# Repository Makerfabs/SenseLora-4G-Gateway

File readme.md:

# SenseLoRa 4G Gateway

```c++
/*
Version:		V1.0
Author:			Vincent
Create Date:	2024/6/19
Note:

*/
```
# Makerfabs

[Makerfabs home page](https://www.makerfabs.com/)

[Makerfabs Wiki](https://wiki.makerfabs.com/)

# How To Use

## Arduino Complier Option

**If you have any questions，such as how to install the development board, how to download the code, how to install the library. Please refer to :[Makerfabs_FAQ](https://github.com/Makerfabs/Makerfabs_FAQ)**

- Install board : ESP32 Version 2.0.11
- Select "ESP32-S3"
- Select Erase All Flash
- Upload codes

Arduino libraries:

- RadioLib 4.6.0

## Example

### fw_test

The factory test program detects whether the AT module can search for the operator and receives Lora data in a loop.

### at_test

Used to debug the AT module and perform transparent serial port transmission.

### lora2thingspeak

The JSON data from the SenseLora Air Monitor is parsed and forwarded to ThingSpeak.

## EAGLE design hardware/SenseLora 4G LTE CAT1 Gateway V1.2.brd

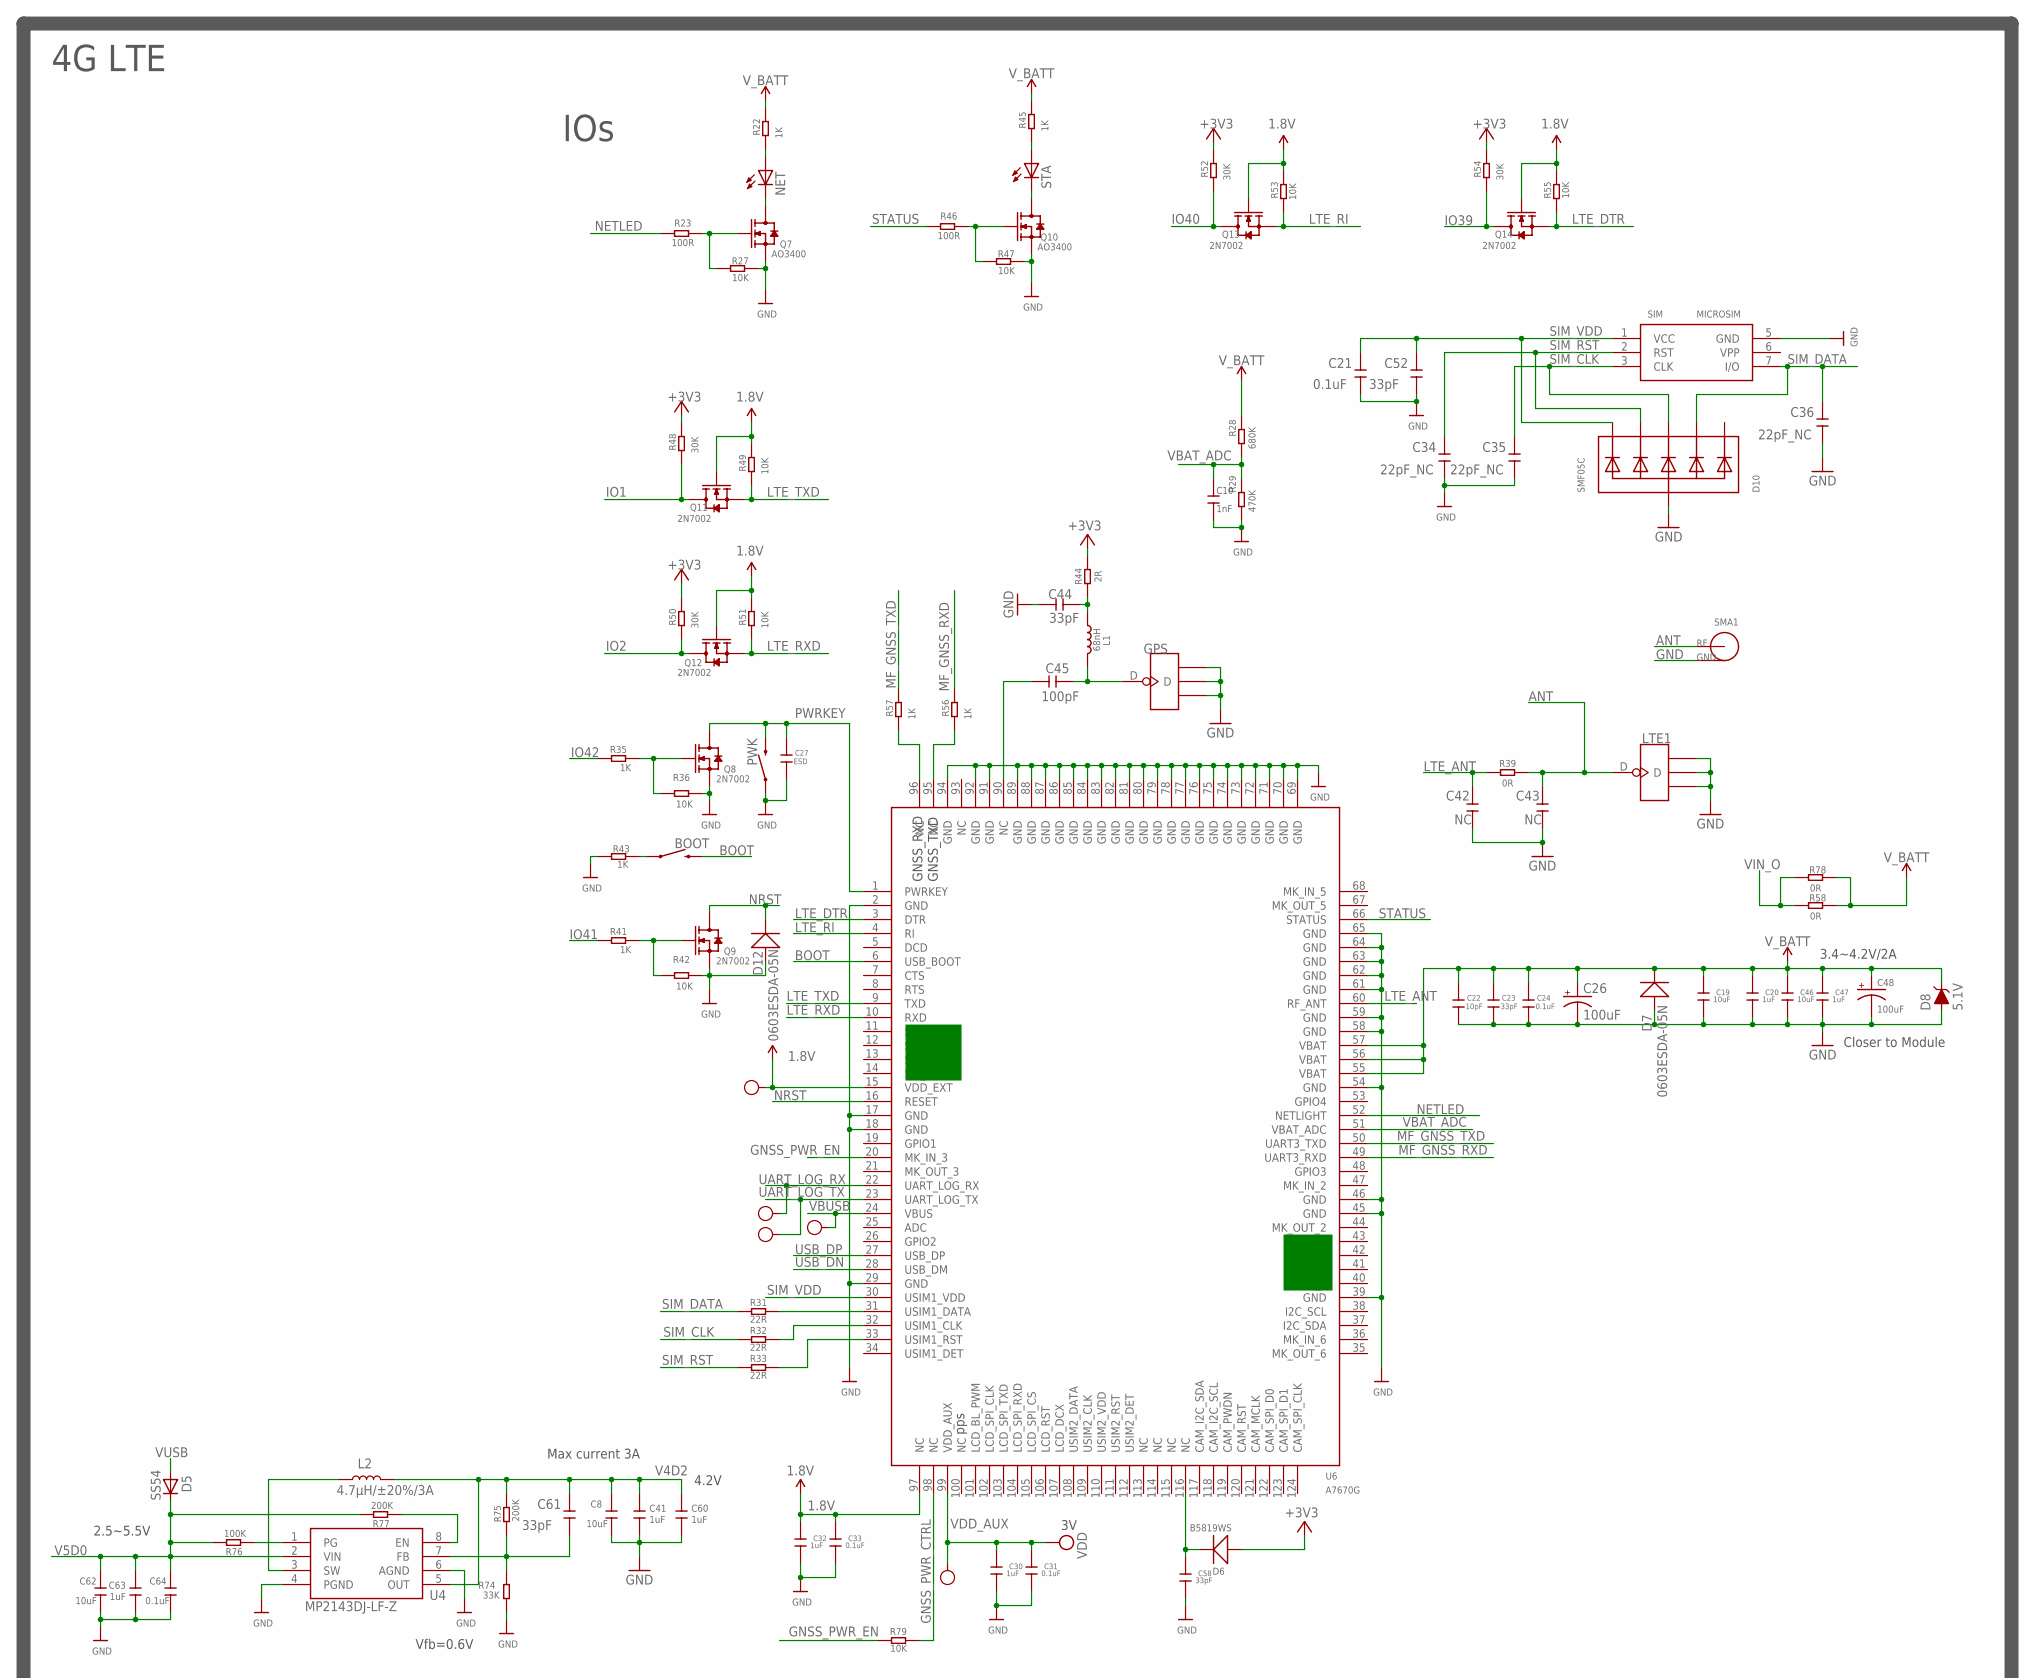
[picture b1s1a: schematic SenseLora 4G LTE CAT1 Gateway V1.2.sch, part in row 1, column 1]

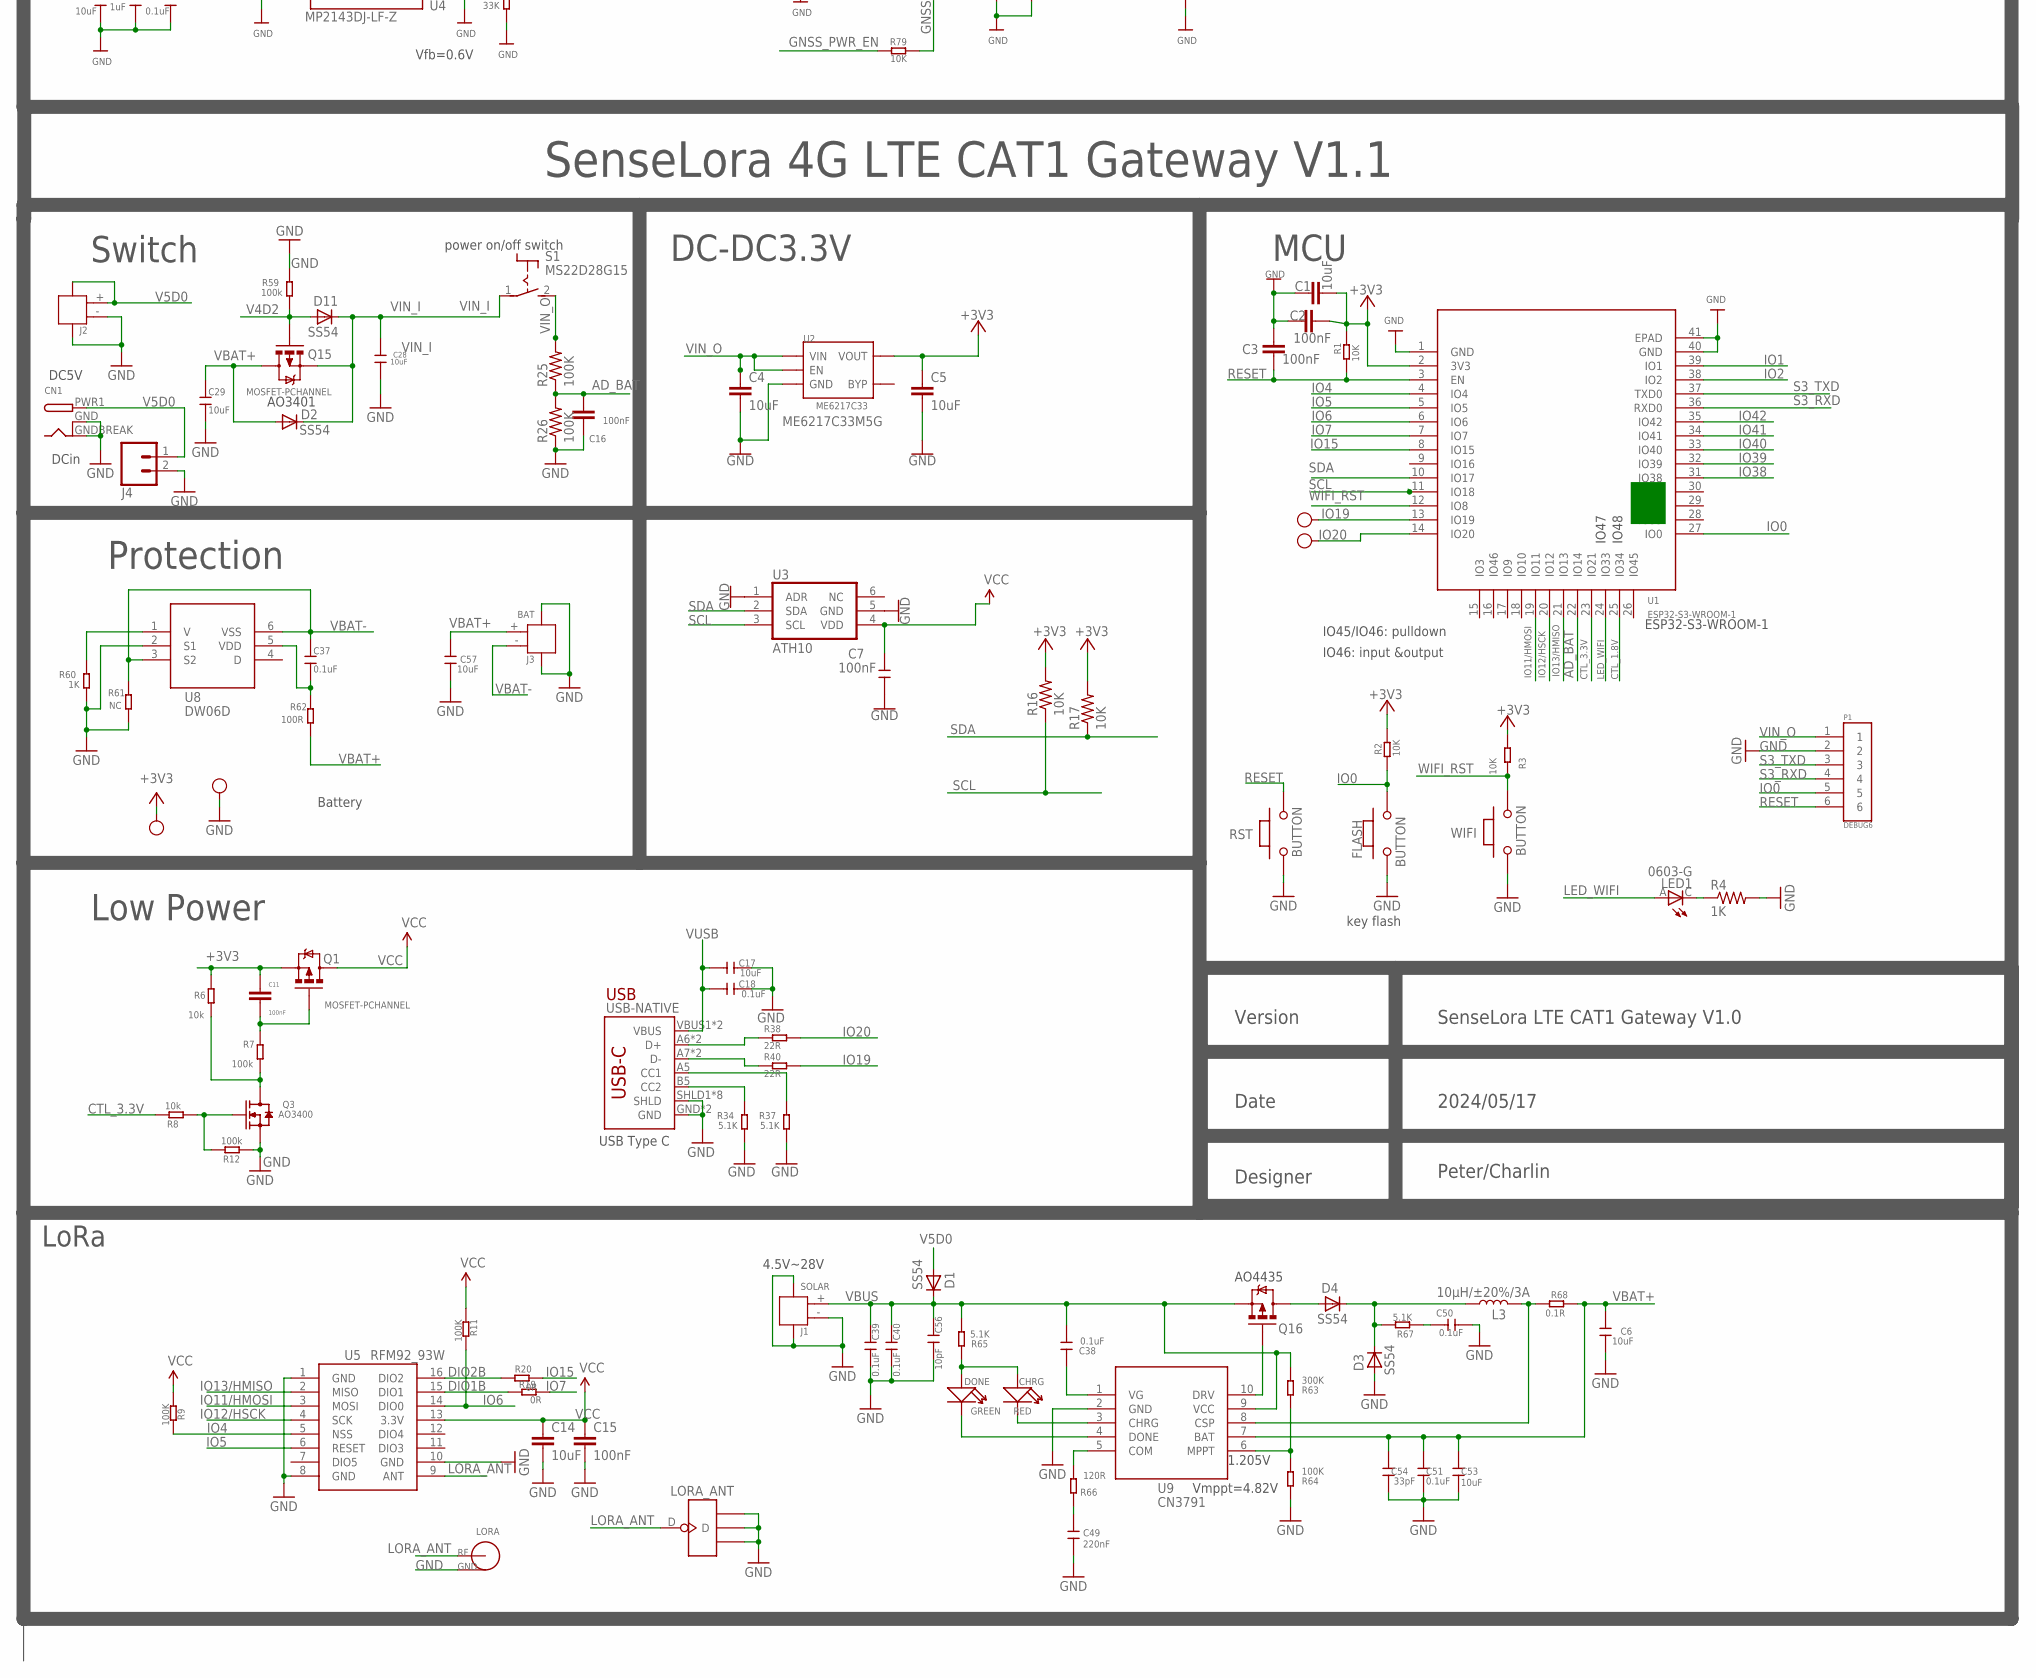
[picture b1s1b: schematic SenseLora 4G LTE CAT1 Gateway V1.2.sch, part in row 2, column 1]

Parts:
1V8, 3V, 3V1, 3V2, 3V3: TEST-POINT'4545'; TP-D45MIL; PARTNO DNP
BOOT: MOMENTARY-SWITCH-SPST-SMD-6.0X3.5MM; TACTILE_SWITCH_SMD_6.0X3.5MM
C1, C4, C5, C14: 10uF; C0603
C2, C3, C11, C15, C16: 100nF; C0603
C6, C53, C57: 10uF; DISCRETE_C0603
C7: 100nF; 0603
C8, C17, C19, C28, C29, C46, C62: 10uF; 0603
C10: 1nF; 0603
C18, C21, C24, C31, C33, C37, C64: 0.1uF; 0603
C20, C30, C32, C41, C47, C60, C63: 1uF; 0603
C22: 10pF; 0603
C23, C44, C52, C58, C61: 33pF; 0603
C26, C48: 100uF; EIA3528
C27: ESD; 0603
C34, C35, C36: 22pF_NC; 0603
C38, C39, C40, C50, C51: 0.1uF; DISCRETE_C0603
C42, C43: NC; 0603
C45: 100pF; 0603
C49: 220nF; DISCRETE_C0603
C54: 33pF; DISCRETE_C0603
C56: 10pF; DISCRETE_C0603
CHRG: RED; LED-0603
CN1: DCBARRELSMT; DCJACK_2MM_SMT
D1, D2, D3, D4, D5, D11: SS54; DO-214AC
D6: B5819WS; SOD323
D7, D12: 0603ESDA-05N; DISCRETE_SOD523
D8: 5.1V; SOD-323
D10: SMF05C; SOT363
DONE: GREEN; LED-0603
FLASH: BUTTON; 157SW
GND: TEST-POINT'4545'; TP-D45MIL; PARTNO DNP
GPS: ANTENNA-U-FL; 4P-U-FL
J1: SOLAR; HW2-SMD-2.0-90D
J2: DC; HW2-SMD-2.0-90D
J3: BAT; HW2-SMD-2.0-90D
J4: CONN_02PTH4; 1X02_XTRA_BIG
L1: 68nH; L0603
L2: 4.7µH/±20%/3A; SRN6045
L3: 10µH/±20%/3A; SRN6045
LED1: 0603-G; LED0603
LORA: SMA-KWE
LORA_ANT: ANTENNA-U-FL; 4P-U-FL
LTE1: ANTENNA-U-FL; 4P-U-FL
NET: NET; CHIP-LED0805
P1: DEBUG6; DEBUG*6
PWK: MOMENTARY-SWITCH-SPST-SMD-6.0X3.5MM; TACTILE_SWITCH_SMD_6.0X3.5MM
Q1, Q15: MOSFET-PCHANNEL; SOT23-3
Q3, Q7, Q10: AO3400; SOT23
Q8, Q9, Q11, Q12, Q13, Q14: 2N7002; SOT23
Q16: MOSFET-PCHANNELFDS6675; SO08
R1, R2, R3, R16, R17, R27, R36, R42, R47, R49, R51, R53, R55, R79: 10K; R0603
R4, R22, R35, R41, R43, R45, R56, R57, R60: 1K; R0603
R6, R8: 10k; R0603
R7, R12, R59: 100k; R0603
R9, R11, R25, R26, R76: 100K; R0603
R19, R20, R39, R58, R78: 0R; R0603
R23, R46, R62: 100R; R0603
R28: 680K; R0603
R29: 470K; R0603
R31, R32, R33, R38, R40: 22R; R0603
R34, R37: 5.1K; R0603
R44: 2R; R0603
R48, R50, R52, R54: 30K; R0603
R61: NC; R0603
R63: 300K; DISCRETE_R0603
R64: 100K; DISCRETE_R0603
R65, R67: 5.1K; DISCRETE_R0603
R66: 120R; DISCRETE_R0603
R68: 0.1R; DISCRETE_R2512
R74: 33K; R0603
R75, R77: 200K; R0603
RST: BUTTON; 157SW
RX: TEST-POINT'4545'; TP-D45MIL; PARTNO DNP
S1: MS22D28G15; S-MS22D28G15
SIM: MICROSIM
SMA1: SMA-KWE
STA: NET; CHIP-LED0805
TX: TEST-POINT'4545'; TP-D45MIL; PARTNO DNP
U1: ESP32-S3-WROOM-1; ESP32-­S2-­SOLO
U2: ME6217C33; SOT23-5
U3: ATH10; AHT10
U4: MP2143DJ-LF-Z; TSOT23-8
U5: RFM92_93W
U6: A7670G
U8: DW06D; SOT-23-6
U9: CN3791; SSOP-10-150MIL
USB-NATIVE: USB_C5; USB-C-16P-5
VU: TEST-POINT'4545'; TP-D45MIL; PARTNO DNP
WIFI: BUTTON; 157SW

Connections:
1.8V: 1V8.T, C32.2, C33.2, Q11.1 (G), Q12.1 (G), Q13.1 (G), Q14.1 (G), R49.2, R51.2, R53.2, R55.2, U6.15 (VDD_EXT), U6.97 (NC)
+3V3: 3V3.T, C1.2, C2.2, C5.1, C11.1, D6.+, Q1.2 (S), R1.2, R2.2, R3.2, R6.2, R16.2, R17.2, R44.2, R48.2, R50.2, R52.2, R54.2, U1.2 (3V3), U2.5 (VOUT)
AD_BAT: C16.2, R25.1, R26.2, U1.22 (IO14)
ANT: C43.2, LTE1.D, R39.2, SMA1.1 (SIG)
BOOT: BOOT.2, U6.6 (USB_BOOT)
CTL_1.8V: U1.25 (IO34)
CTL_3.3V: R8.2, U1.23 (IO21)
DIO1B: R19.2, U5.15 (DIO1)
DIO2B: R20.2, U5.16 (DIO2)
GND: C1.1, C2.1, C3.2, C4.2, C5.2, C6.2, C7.1, C8.1, C10.2, C14.2, C15.2, C16.1, C17.2, C18.2, C19.1, C20.1, C21.1, C22.1, C23.1, C24.1, C26.C (-), C27.1, C28.1, C29.2, C30.1, C31.1, C32.1, C33.1, C34.1, C35.1, C36.1, C39.2, C40.2, C41.1, C42.1, C43.1, C44.2, C46.1, C47.1, C48.C (-), C49.2, C50.2, C51.2, C52.1, C53.2, C54.2, C56.2, C57.2, C58.1, C60.1, C62.1, C63.1, C64.1, CN1.GND (GNDBREAK), CN1.GNDBREAK (GND), D3.A, D7.+, D8.A, D10.2 (A), D12.+, FLASH.1, GND.T, GPS.GND1, GPS.GND2, GPS.GND3, J1.3, J1.4, J1.- (2), J2.3, J2.- (2), J3.3, J3.4, J4.2, LORA.2 (GND), LORA.3 (GND), LORA.4 (GND), LORA.5 (GND), LORA_ANT.GND1, LORA_ANT.GND2, LORA_ANT.GND3, LTE1.GND1, LTE1.GND2, LTE1.GND3, P1.2, PWK.1, Q3.2 (S), Q7.2 (S), Q8.2 (S), Q9.2 (S), Q10.2 (S), R4.2, R12.1, R26.1, R27.1, R29.1, R34.1, R36.1, R37.1, R42.1, R43.2, R47.1, R59.2, R60.1, R61.1, R64.1, R74.1, RST.1, SIM.5 (GND), SMA1.2 (GND), SMA1.3 (GND), SMA1.4 (GND), SMA1.5 (GND), U1.1 (GND), U1.40 (GND), U1.41 (EPAD), U2.2 (GND), U3.1 (ADR), U3.5 (GND), U4.4 (PGND), U4.6 (AGND), U5.1 (GND), U5.8 (GND), U5.10 (GND), U6.2 (GND), U6.17 (GND), U6.18 (GND), U6.29 (GND), U6.39 (GND), U6.45 (GND), U6.46 (GND), U6.54 (GND), U6.58 (GND), U6.59 (GND), U6.61 (GND), U6.62 (GND), U6.63 (GND), U6.64 (GND), U6.65 (GND), U6.69 (GND), U6.70 (GND), U6.71 (GND), U6.72 (GND), U6.73 (GND), U6.74 (GND), U6.75 (GND), U6.76 (GND), U6.77 (GND), U6.78 (GND), U6.79 (GND), U6.80 (GND), U6.81 (GND), U6.82 (GND), U6.83 (GND), U6.84 (GND), U6.85 (GND), U6.86 (GND), U6.87 (GND), U6.88 (GND), U6.89 (GND), U6.91 (GND), U6.92 (GND), U6.94 (GND), U8.2 (S1), U9.2 (GND), USB-NATIVE.GND, USB-NATIVE.GND2 (GND), USB-NATIVE.SHLD1 (SHLD), USB-NATIVE.SHLD2 (SHLD), USB-NATIVE.SHLD3 (SHLD), USB-NATIVE.SHLD4 (SHLD), USB-NATIVE.SHLD5 (SHLD), USB-NATIVE.SHLD6 (SHLD), USB-NATIVE.SHLD7 (SHLD), USB-NATIVE.SHLD8 (SHLD), WIFI.1
GNSS_PWR_CTRL: R79.1, U6.98 (NC)
GNSS_PWR_EN: R79.2, U6.20 (MK_IN_3)
IO0: FLASH.2, P1.5, R2.1, U1.27 (IO0)
IO1: Q11.3 (D), R48.1, U1.39 (IO1)
IO2: Q12.3 (D), R50.1, U1.38 (IO2)
IO4: R9.1, U1.4 (IO4), U5.5 (NSS)
IO5: U1.5 (IO5), U5.6 (RESET)
IO6: R11.1, U1.6 (IO6), U5.14 (DIO0)
IO7: R19.1, U1.7 (IO7)
IO11/HMOSI: U1.19 (IO11), U5.3 (MOSI)
IO12/HSCK: U1.20 (IO12), U5.4 (SCK)
IO13/HMISO: U1.21 (IO13), U5.2 (MISO)
IO15: R20.1, U1.8 (IO15)
IO19: 3V1.T, R40.1, U1.13 (IO19)
IO20: 3V2.T, R38.1, U1.14 (IO20)
IO38: U1.31 (IO38)
IO39: Q14.3 (D), R54.1, U1.32 (IO39)
IO40: Q13.3 (D), R52.1, U1.33 (IO40)
IO41: R41.2, U1.34 (IO41)
IO42: R35.2, U1.35 (IO42)
LED_WIFI: LED1.A, U1.24 (IO33)
LORA_ANT: LORA.1 (SIG), LORA_ANT.D, U5.9 (ANT)
LTE_ANT: C42.2, R39.1, U6.60 (RF_ANT)
LTE_DTR: Q14.2 (S), R55.1, U6.3 (DTR)
LTE_RI: Q13.2 (S), R53.1, U6.4 (RI)
LTE_RXD: Q12.2 (S), R51.1, U6.10 (RXD)
LTE_TXD: Q11.2 (S), R49.1, U6.9 (TXD)
MF_GNSS_RXD: R56.2, U6.49 (UART3_RXD)
MF_GNSS_TXD: R57.2, U6.50 (UART3_TXD)
unnamed: LED1.C, R4.1
unnamed: Q7.1 (G), R23.1, R27.2
unnamed: NET.C, Q7.3 (D)
unnamed: NET.A, R22.1
unnamed: Q16.4 (G), U9.10 (DRV)
unnamed: BOOT.1, R43.1
unnamed: Q10.1 (G), R46.1, R47.2
unnamed: C37.2, R62.2, U8.5 (VDD)
unnamed: C11.2, Q1.1 (G), R7.2
unnamed: Q3.1 (G), R8.1, R12.2
unnamed: R60.2, U8.1 (V)
unnamed: R63.1, R64.2, U9.6 (MPPT)
unnamed: Q3.3 (D), R6.1, R7.1
unnamed: C58.2, D6.-, U6.116 (NC)
unnamed: C38.2, U9.1 (VG)
unnamed: CHRG.+, DONE.+, R65.1
unnamed: R31.1, U6.31 (USIM1_DATA)
unnamed: R32.1, U6.32 (USIM1_CLK)
unnamed: R33.1, U6.33 (USIM1_RST)
unnamed: CHRG.-, U9.3 (CHRG)
unnamed: L2.1, U4.3 (SW)
unnamed: R37.2, USB-NATIVE.A5 (CC1)
unnamed: R34.2, USB-NATIVE.B5 (CC2)
unnamed: R45.1, STA.A
unnamed: Q10.3 (D), STA.C
unnamed: R38.2, USB-NATIVE.A6 (D+), USB-NATIVE.B6 (D+)
unnamed: R40.2, USB-NATIVE.A7 (D-), USB-NATIVE.B7 (D-)
unnamed: Q9.1 (G), R41.1, R42.2
unnamed: C45.2, U6.90 (NC)
unnamed: DONE.-, U9.4 (DONE)
unnamed: R56.1, U6.95 (NC)
unnamed: R57.1, U6.96 (NC)
unnamed: C61.1, R74.2, R75.1, U4.7 (FB)
unnamed: R76.1, U4.1 (PG)
unnamed: R66.2, U9.5 (COM)
unnamed: C49.1, R66.1
unnamed: Q8.1 (G), R35.1, R36.2
unnamed: D4.A, Q16.5 (D), Q16.6 (D), Q16.7 (D), Q16.8 (D)
unnamed: D3.C, D4.C, L3.1, R67.2
unnamed: L3.2, R68.1, U9.8 (CSP)
unnamed: C50.1, R67.1
unnamed: R77.1, U4.8 (EN)
unnamed: C44.1, L1.1, R44.1
unnamed: C45.1, GPS.D, L1.2
NETLED: R23.2, U6.52 (NETLIGHT)
NRST: D12.-, Q9.3 (D), U6.16 (RESET)
PWRKEY: C27.2, PWK.2, Q8.3 (D), U6.1 (PWRKEY)
RESET: C3.1, P1.6, R1.1, RST.2, U1.3 (EN)
S3_RXD: P1.4, U1.36 (RXD0)
S3_TXD: P1.3, U1.37 (TXD0)
SCL: R16.1, U1.11 (IO18), U3.3 (SCL)
SDA: R17.1, U1.10 (IO17), U3.2 (SDA)
SIM_CLK: C35.2, D10.4 (C3), R32.2, SIM.3 (CLK)
SIM_DATA: C36.2, D10.3 (C2), R31.2, SIM.7 (I/O)
SIM_RST: C34.2, D10.5 (C4), R33.2, SIM.2 (RST)
SIM_VDD: C21.2, C52.2, D10.6 (C5), SIM.1 (VCC), U6.30 (USIM1_VDD)
STATUS: R46.2, U6.66 (STATUS)
UART_LOG_RX: RX.T, U6.22 (UART_LOG_RX)
UART_LOG_TX: TX.T, U6.23 (UART_LOG_TX)
USB_DN: U6.28 (USB_DM)
USB_DP: U6.27 (USB_DP)
V4D2: C8.2, C41.2, C60.2, C61.2, D11.A, L2.2, Q15.1 (G), R59.1, R75.2, U4.5 (OUT)
V5D0: C62.2, C63.2, C64.2, CN1.PWR1 (PWR), D1.A, D5.C, J2.4, J2.+ (1), J4.1, R76.2, R77.2, U4.2 (VIN)
VBAT+: C6.1, C29.1, C51.1, C53.1, C54.1, C57.1, D2.A, J3.+ (1), Q15.3 (D), R62.1, R68.2, U9.7 (BAT)
VBAT-: C37.1, J3.- (2), R61.2, U8.3 (S2), U8.6 (VSS)
VBAT_ADC: C10.1, R28.1, R29.2, U6.51 (VBAT_ADC)
VBUS: C38.1, C39.1, C40.1, C56.1, D1.C, J1.+ (1), Q16.1 (S), Q16.2 (S), Q16.3 (S), R63.2, R65.2, U9.9 (VCC)
VBUSB: U6.24 (VBUS), VU.T
VCC: C7.2, C14.1, C15.1, Q1.3 (D), R9.2, R11.2, U3.4 (VDD), U5.13 (3.3V)
VDD_AUX: 3V.T, C30.2, C31.2, U6.99 (VDD_AUX)
VIN_I: C28.2, D2.C, D11.C, Q15.2 (S), S1.1
VIN_O: C4.1, P1.1, R25.2, R58.2, R78.2, S1.2 (S), U2.1 (VIN), U2.3 (EN)
VUSB: C17.1, C18.1, D5.A, USB-NATIVE.VBUS1 (VBUS), USB-NATIVE.VBUS2 (VBUS)
V_BATT: C19.2, C20.2, C22.2, C23.2, C24.2, C26.A (+), C46.2, C47.2, C48.A (+), D7.-, D8.C, R22.2, R28.2, R45.2, R58.1, R78.1, U6.55 (VBAT), U6.56 (VBAT), U6.57 (VBAT)
WIFI_RST: R3.1, U1.12 (IO8), WIFI.2

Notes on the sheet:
DC-DC3.3V
ME6217C33M5G
LoRa
power on/off switch
key flash
Switch
MCU
Low Power
IO45/IO46: pulldown
IO46: input &output
ESP32-S3-WROOM-1
IO47
IO48
SenseLora 4G LTE CAT1 Gateway V1.1
Version
Date
Designer
SenseLora LTE CAT1 Gateway V1.0
2024/05/17
Peter/Charlin
IOs
USB
USB Type C
Closer to Module
3.4~4.2V/2A
GNSS_TXD
GNSS_RXD
4G LTE
pps
AO3401
Battery
Protection
4.5V~28V
1.205V
Vmppt=4.82V
AO4435
4.2V
Max current 3A
Vfb=0.6V
2.5~5.5V

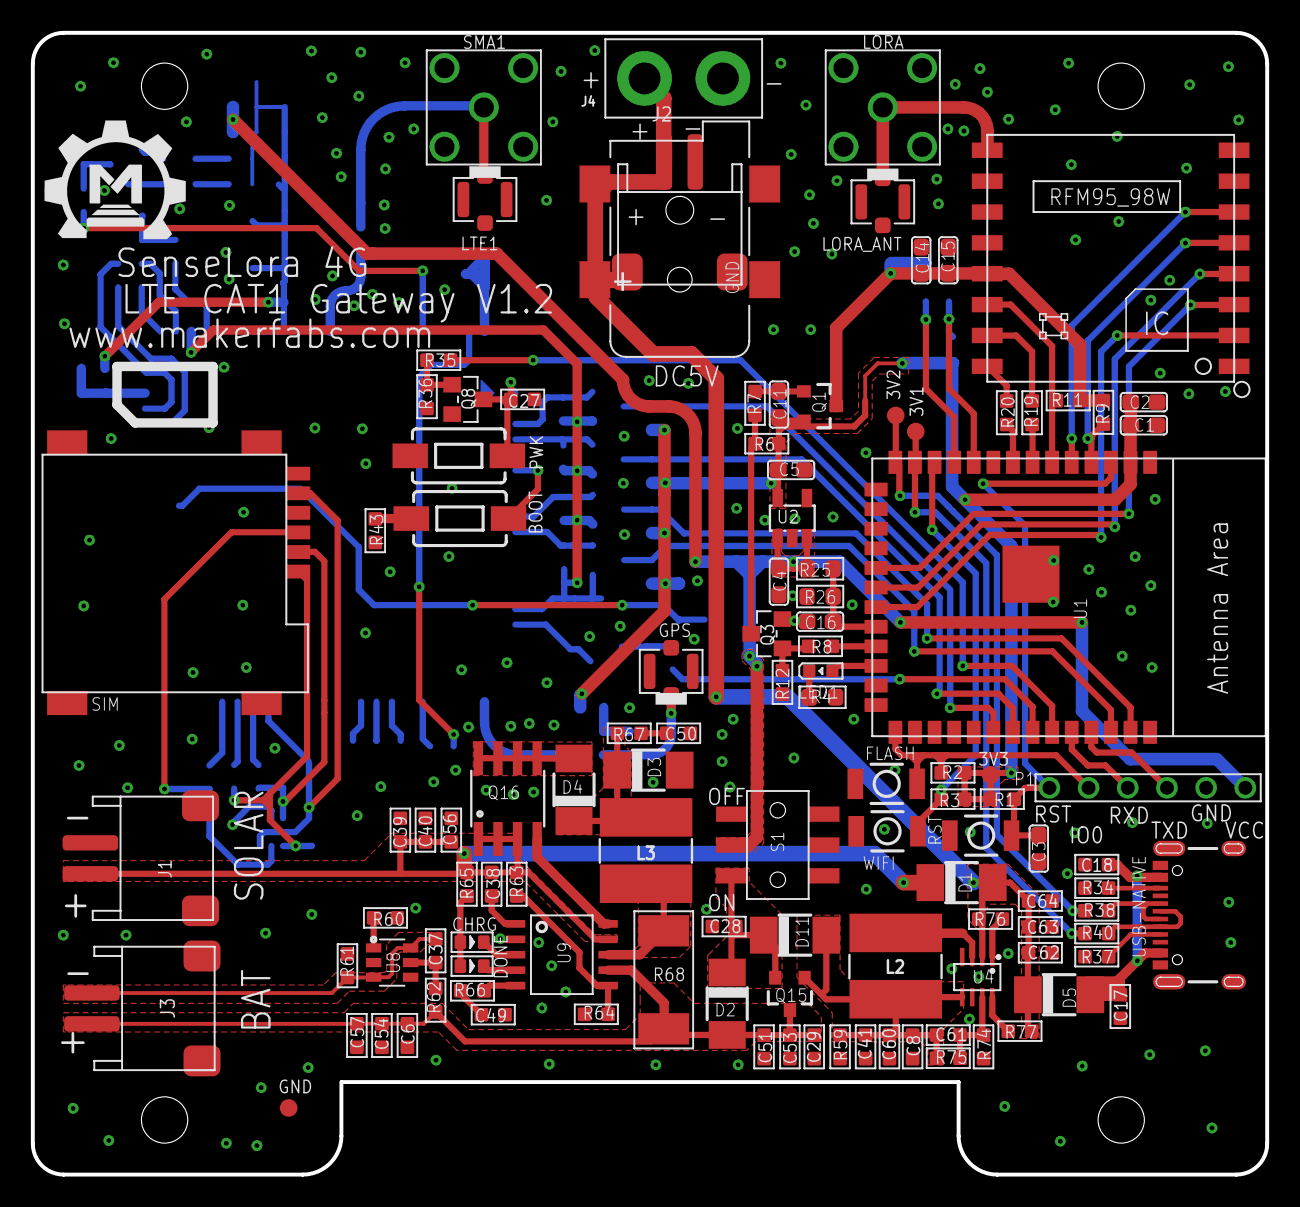
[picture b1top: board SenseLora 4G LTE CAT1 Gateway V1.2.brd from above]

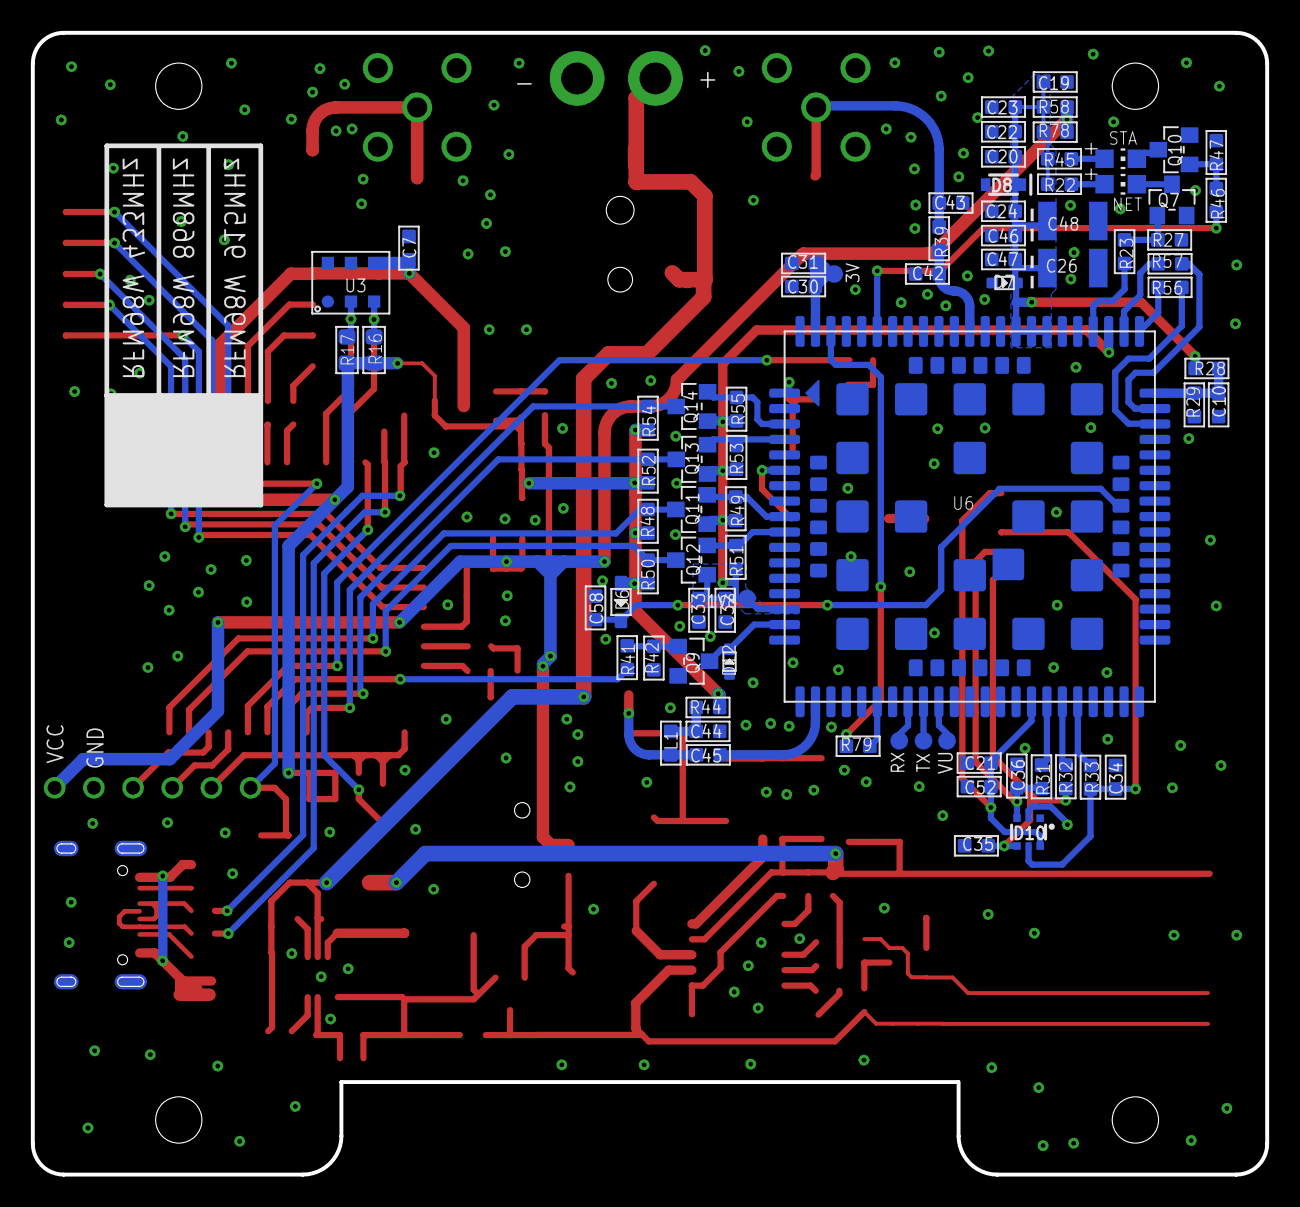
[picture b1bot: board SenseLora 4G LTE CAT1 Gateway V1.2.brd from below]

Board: 2 copper layers, 80.0 x 74.0 mm, 191 parts (77 on the bottom side), 110 nets.

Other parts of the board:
U$2: MAKERFABS_0.3

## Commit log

2024-06-19 Create Project
2024-06-19 Add at demo
2024-06-19 Change Lora settings.
2024-08-17 add demo
2025-08-25 Add hardware v1.2
2026-04-15 Update pin definitions for LoRa module
2026-04-15 Modify LoRa pin definitions
    Updated pin definitions for LoRa module connections.

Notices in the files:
parts and their libraries:
User-Submitted: Licensing: Creative Commons ShareAlike 4.0 International - https://creativecommons.org/licenses/by-sa/4.0
microbuilder: This work is placed in the public domain, and may be freely used for commercial and non-commercial work with the following conditions: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
